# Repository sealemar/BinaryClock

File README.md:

BinaryClock
===========

More about the project is on my blog:

- [I talk about software](http://sealemar.blogspot.com/2014/02/binaryclock-binary-clock-diy.html)
- [I talk about hardware](http://sealemar.blogspot.com/2014/02/binaryclock-hardware.html)

Here I talk only about the tools which you will need to compile the software.

Tools I will need
-----------------

This is a list of tools you will (or may) need to work with the code. This list is described in more details on the [blog](http://sealemar.blogspot.com).

- [Make](http://www.gnu.org/software/make/manual/make.html) (*comes with every Unix based OS - Linux/Mac, etc.*)
- [Arduino software](http://arduino.cc/en/Main/Software)
- [Makefile by Sudar / Martin Oldfield](https://github.com/sudar/Arduino-Makefile)
- [colorgcc](https://github.com/colorgcc/colorgcc) (*optional, but is very handy when it comes to compiling code in the console/terminal*)
- [Exuberant ctags](http://ctags.sourceforge.net/) (*optional, but is very handy especially when it comes to Emacs or ViM*)

**For the emulator and tests:**
- gcc / clang (*at least one of these comes with every Unix based OS - Linux - gcc, MacOs - clang*)

**For the emulator:**
- ncurses (*comes with every Unix based OS*)

**For the vimproject (optional - read on):**
- ViM, [MacVim](https://code.google.com/p/macvim) for Mac

**For the schematic:**
- [Fritzing](http://fritzing.org)

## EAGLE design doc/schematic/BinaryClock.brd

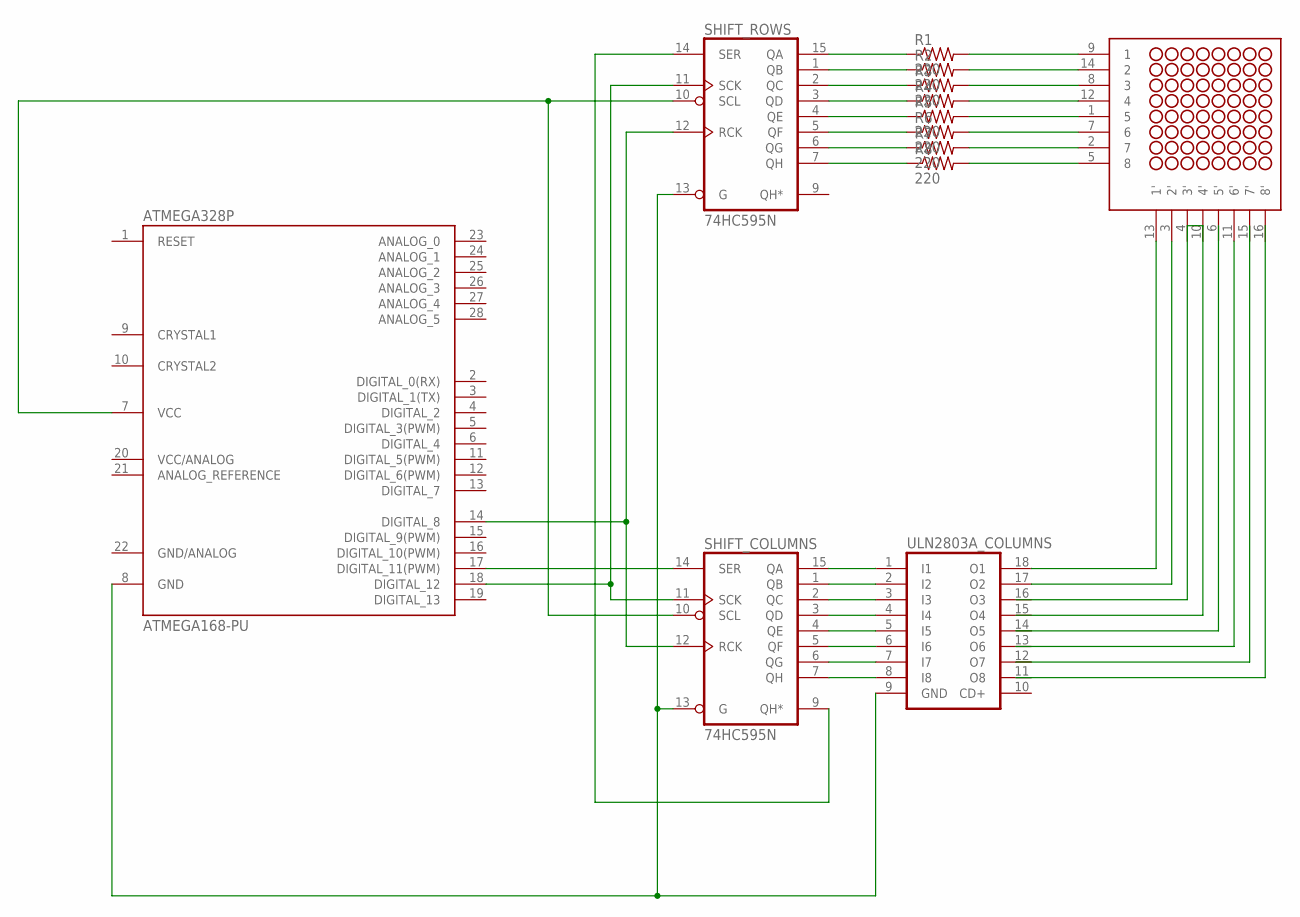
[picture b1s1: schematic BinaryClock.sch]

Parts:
ATMEGA328P: ATMEGA168-PU; DIL28-3
LD1088BS: NFM-12881BG-11
R1, R2, R3, R5, R6, R7, R8: 220; 0207/10
R4: R-US_0207/10; 0207/10
SHIFT_COLUMNS: 74HC595N; DIL16
SHIFT_ROWS: 74HC595N; DIL16
ULN2803A_COLUMNS: ULN2803A; DIL18

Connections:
GND: SHIFT_COLUMNS.8 (GND), SHIFT_ROWS.8 (GND)
GND/ANALOG: ATMEGA328P.22 (GND/ANALOG)
unnamed: SHIFT_COLUMNS.9 (QH*), SHIFT_ROWS.14 (SER)
unnamed: ATMEGA328P.17 (DIGITAL_11(PWM)), SHIFT_COLUMNS.14 (SER)
unnamed: ATMEGA328P.18 (DIGITAL_12), SHIFT_COLUMNS.11 (SCK), SHIFT_ROWS.11 (SCK)
unnamed: ATMEGA328P.14 (DIGITAL_8), SHIFT_COLUMNS.12 (RCK), SHIFT_ROWS.12 (RCK)
unnamed: LD1088BS.14 (2), R2.2
unnamed: SHIFT_COLUMNS.15 (QA), ULN2803A_COLUMNS.1 (I1)
unnamed: SHIFT_COLUMNS.1 (QB), ULN2803A_COLUMNS.2 (I2)
unnamed: SHIFT_COLUMNS.2 (QC), ULN2803A_COLUMNS.3 (I3)
unnamed: SHIFT_COLUMNS.3 (QD), ULN2803A_COLUMNS.4 (I4)
unnamed: SHIFT_COLUMNS.4 (QE), ULN2803A_COLUMNS.5 (I5)
unnamed: SHIFT_COLUMNS.5 (QF), ULN2803A_COLUMNS.6 (I6)
unnamed: SHIFT_COLUMNS.6 (QG), ULN2803A_COLUMNS.7 (I7)
unnamed: SHIFT_COLUMNS.7 (QH), ULN2803A_COLUMNS.8 (I8)
unnamed: ATMEGA328P.7 (VCC), SHIFT_COLUMNS.10 (SCL), SHIFT_ROWS.10 (SCL)
unnamed: R2.1, SHIFT_ROWS.1 (QB)
unnamed: R3.1, SHIFT_ROWS.2 (QC)
unnamed: R4.1, SHIFT_ROWS.3 (QD)
unnamed: R5.1, SHIFT_ROWS.4 (QE)
unnamed: R6.1, SHIFT_ROWS.5 (QF)
unnamed: R7.1, SHIFT_ROWS.6 (QG)
unnamed: R8.1, SHIFT_ROWS.7 (QH)
unnamed: R1.1, SHIFT_ROWS.15 (QA)
unnamed: ATMEGA328P.8 (GND), SHIFT_COLUMNS.13 (G), SHIFT_ROWS.13 (G), ULN2803A_COLUMNS.9 (GND)
unnamed: LD1088BS.8 (3), R3.2
unnamed: LD1088BS.12 (4), R4.2
unnamed: LD1088BS.1 (5), R5.2
unnamed: LD1088BS.7 (6), R6.2
unnamed: LD1088BS.2 (7), R7.2
unnamed: LD1088BS.5 (8), R8.2
unnamed: LD1088BS.9 (1), R1.2
unnamed: LD1088BS.13 (1'), ULN2803A_COLUMNS.18 (O1)
unnamed: LD1088BS.3 (2'), ULN2803A_COLUMNS.17 (O2)
VCC: SHIFT_COLUMNS.16 (VCC), SHIFT_ROWS.16 (VCC)

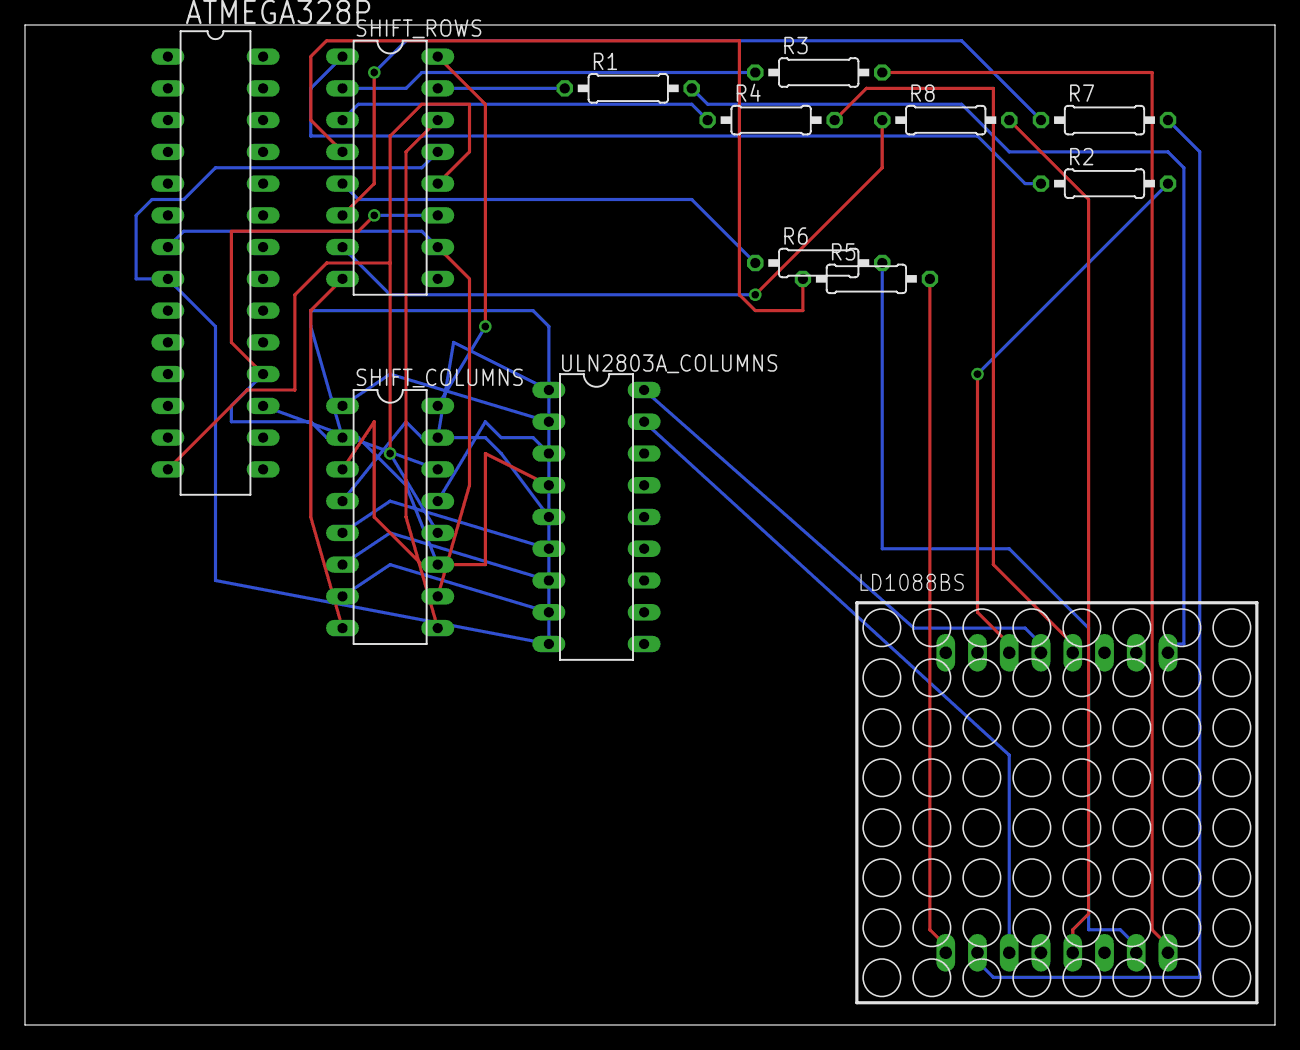
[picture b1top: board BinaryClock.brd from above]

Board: 2 copper layers, 100.0 x 80.0 mm, 13 parts (0 on the bottom side), 34 nets.

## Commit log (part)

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2013-11-09 introducing API, alphabet
2013-11-11 +) YouCompleteMe +) Added subdirectories: arduino, lib, emulator, test, include each of those have their own Makefile +) unit tests for clock::slidePattern()
2013-11-11 *) mainly work around Makefiles *) *.o -> obj/*.o *) *.d -> deps/*.d *) project.vim now creates etc/ dir when saving a session
2013-11-12 +) .gitignore + etc/ *) silent include dependencies and only if rule is not "clean" *) test/tests.c doesn't need #include <arch/clock_bits.h>
2013-11-12 +) .gitignore bin/, obj/, dep/ *) ar -v
2013-11-13 *) Now Makefile creates supplimentary directories only once
2013-11-13 +) Trying to make emulator to call clock_drawPattern()
2013-11-14 *) Makefile changes to make it compile and link on Raspberry Pi (ARM) as well as on x86
2013-11-14 *) Removed separate definition and switched from gcc back to clang
2013-11-14 +) Makefile distclean target. make clean - removes object files, dependency files, binaries make distclean - removes BUILD_DIR if set or OBJ_DIR, BIN_DIR, DEPS_DIR and ctags file
2013-11-14 *) Emulator works and draws the alphabet. To draw one character back press 'h' or 'k', to draw one character forward press any other key. Press Esc to quit
2013-11-15 *) This change reverses the patterns to bits counting from right to left
2013-11-15 +) lib/clock::clock_slideText() +) lib/clock::clock_slidePattern() *) Makefile.include always create ctags file
2013-11-15 +) Clock can slide any text. "Hello world!!!" sliding is implemented
2013-11-15 +) include/Makefile.include + -include stddef.h ---> got read of #define NULL 0
2013-11-15 +) lib/clock.c::clock_displayBinaryNumber() - not working yet
2013-11-15 lib/clock.c::clock_displayBinaryNumber() works correctly
2013-11-16 +) A little testing framework was implemented which produces this kind of output:
    --- tests.c:21 (main) - a test suite started ---
    --- ut_clock.c:239 (ut_clock_tests) - a test suite started ---
    Error: ut_clock.c:172 (test_clock_drawPattern_correct) - [-48] pattern CLOCK_ALPHABET[CLOCK_1] doesn't match the screen
    ----> test_ut/test_ut.c:21 (_runTestSuite) - [-48]
    --- ut_clock.c:239 (ut_clock_tests) - a test suite completed --- 4 test(s) ran. 3 succeded, 1 failed
    ----> test_ut/test_ut.c:21 (_runTestSuite) - [1]
2013-11-18 *) test_ut now prints which unit it currently runs
2013-11-18 +) lib/clock_time - working on the Binary Clock date/time functionality
2013-11-19 -) lib/arch/*, emulator/arch/*, test/arch/* Now clock_setPixel() is defined directly in lib/clock.h for simplicity
    +) test/.ycm_extra_conf.py - a separate YouCompleteMe configuration for
    tests
2013-11-19 +) test/ut_clock_time --- unit tests for lib/clock_time.c:clock_updateUptimeMillis()
    *) .ycm_extra_conf.py seems to handle sorces correctly now
2013-11-19 *) lib/clock_time.c::DateTime now has milliseconds +) unit tests for lib/clock_time.c::clock_addMillisToDateTime()
2013-11-20 +) A separate module which incapsulates DateTime functionality
    *) A unit test for dateTime_addMilliseconds() was rewritten to work with
    a new module
2013-11-20 +) test_dateTime_normalize_handlesOverflows()
2013-11-22 *) test/ut_date_time.c - underflows
2013-11-25 +) include/common.h --- version information +) emulator --- sections: - Banner - ClockFace - Buttons - Notes
2013-11-25 +) emulator/clock_extra --- buttons
2013-11-27 +) include/common.h::Call() -- a macro Call(function) makes a function call taking PARAM_CHECKS macro into consideration. If the macro is defined, ContinueError(functionResult, "%d"); will be called 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
    +) lib/clock_state.h -- clock state to pass with every iteration of main
    loop
    +) lib/clock_main -- working on clock_update(ClockState *) function
    which will be called from main loop
    *) lib/clock_time::clock_updateUptimeMillis() now takes a pointer to
    unsigned long to get and set lastMillis
2013-11-27 The first somewhat working version of BinaryClock emulator!!! At startup it shows a banner, then starts Binary Clock mode
    +) lib/clock_main::clock_init()
    +) lib/clock_main::clock_state_*() implementation of some functions
2013-11-27 *) Optimization of clock_state_showTime() and clock_state_showDate() by adding ClockState::oldDateTime. ClockState::dateTime gets updated at the beginning of clock_update() and ClockState::oldDateTim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
2013-11-27 *) Working towards implementation for the buttons
2013-11-27 *) Working towards implementation of the buttons
2013-11-28 +) lib/clock_button and corresponding unit tests. Current implementation can operate on up to 4 buttons
2013-11-28 +) emulator/emulator_button -- buttons work. Not connected yet
2013-11-28 +) lib/clock_state::ClockState.frameMillis -- current frame time (for animation), i.e. those steps which slide text can use it to show the next frame only after the _frameMillis_ exceeds some amount
2013-11-28 +) lib/clock_main::clock_state_setTime()
2013-11-29 *) lib/clock_main::clock_state_setTime() blinks time while it is being set
2013-11-29 +) emulator/emulator_button -- now displays information next to each button with what that button does in the current context
2013-11-29 +) lib/date_time::date_time_dateToStr(const DateTime *dt, char str[DATE_TIME_DATE_STR_SIZE]) prints date from _dt_ to _str_ in format MMM DD YYYY
    +) lib/date_time::date_time_timeToStr(const DateTime *dt, char str[DATE_TIME_TIME_STR_SIZE])
    prints time from _dt_ to _str_ in format
    hh:mm:ss
    +) unit tests for both functions
    +) lib/date_time::DateTimeMonthsStr --- an array of three letter months
2013-11-29 +) lib/clock_main::clock_state_showTimeBigEndian()
2013-11-30 +) lib/date_time::date_time_daysInMonth() returns a quantity of days in a month
    +) test/test_ut/test_ut.h::assert_number(number, expected) asserst any number against
    expected
    +) test/test_ut/test_ut.h::assert_errorCode(function, expectedErrorCode)
    asserts a function against an expected error code
2013-11-30 *) include/Makefile.include::CC_c_FLAGS + -Wextra -Werror
    *) test/test_ut/test_ut.h::assert_errorCode -> assert_function
2013-11-30 *) All extern functions which an implementation must or may want to (for some funcitons) override are now declared in lib/clock_extern_functions.h and stubbed to NULL by default
    +) lib/clock_extern_functions.c::clock_initDateTime(DateTime *) an
    implementation may define this function. If it is not NULL,
    lib/clock_main.c::clock_init(ClockState *) will call it to initialize
    ClockState->DateTime. I.e. an implementation may define the function to
    set the date and time to current date and time
2013-11-30 +) lib/clock_extern::clock_extern_clearScreen(). The implementation may override this to optimize clock_clearScreen() behavior. By default it does Call( clock_drawPattern(ClockAlphabet[CLOCK_BLANK]) 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
    *) Refactoring
2013-11-30 +) More Call*() macros
2013-11-30 *) Call*() around some more functions, which I missed in the last commit
2013-12-01 +) -D _BSD_SOURCE in emulator/Makefile for localtime_r() on Linux
2013-12-01 +) lib/clock_main added segue from CLOCK_STATE_SHOW_TIME_BIG_ENDIAN to CLOCK_STATE_SHOW_DATE_BIG_ENDIAN and vice versa
2013-12-02 +) working on lib/clock_events
    +) lib/clock_alphabet + '(' and ')'
    +) lib/clock_alphabet::clock_alphabet_getIndexByCharacter() now
    recognizes
    SMILEY_FACE_SMILE - '\001'
    SMILEY_FACE_SAD - '\002'
    *) lib/clock::clock_getAlphabetIndexByCharacter() ->
2013-12-03 *) Still working on lib/clock_events
2013-12-04 *) minor changes to lib/clock_event.h macros
2013-12-04 +) test/test_ut/test_ut.h::assert_false()
2013-12-05 *) Makefile -- don't cancel make job if Arduino make fails
2013-12-05 +) lib/date_time::date_time_calculateDayOfWeek(int year, int month, int day)
    implemented using
    Gauss's algorithm
    to determine day of week in Gregorian Calendar
    http://en.wikipedia.org/wiki/Determination_of_the_day_of_the_week#Formulas_derived_from_Gauss.27s_algorithm
    +) unit tests
    +) some changes to lib/clock_event
2013-12-05 *) fixed typos in functions' names
2013-12-06 !! This is an intermediate version !! Can not be compiled
    *) working on lib/clock_event
    -) lib/date_const
    +) lib/date_time strings for days of week
    *) lib/date_time::date_time_daysInMonth() now takes year and month
    separately, instead of taking a pointer to DateTime
2013-12-07 *) working on lib/clock_event +) test_clock_event_getEventDetails_correct() *) fixed some compilation issues with PARAM_CHECKS off *) fixed a bug in lib/date_time.c::_dayOfWeek() in Gauss's algorithm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
2013-12-07 +) test/ut_clock_event::test_clock_event_initList_correct() +) test/ut_clock_event::test_clock_event_updateList_correct()
    *) some unit tests in test/ut_clock_event were changed to have data
    declaration in the beginning and then code checking the data in the end
    +) ut_test -- assert_number_ex(), assert_int_ex(), assert_str_ex()
2013-12-07 +) lib/clock_event::ClockEvent.yearCalculated -- the year which the event is calculated for (initially CLOCK_EVENT_YEAR_NOT_CALCULATED)
    *) lib/clock_event::ClockEvent.year ->
    lib/clock_event::ClockEvent.yearStarted
2013-12-09 +) lib/clock_alphabet::CLOCK_TICK --- "'" +) lib/clock_event::clock_event_toStr() +) lib/clock_event::clock_event_findClosestFromList() +) lib/clock_main::checkButton() macro +) lib/clock_main::clock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
    *) lib/clock_main::slideText() now accepts an optional callback which should be
    called when the slideText() completes. If it is not NULL, _nextState_ and
    _nextStepMillis_ will be ignored and the callback will be called.
2013-12-09 *) fixed comments for ClockEvent.name size
2013-12-09 *) comments
2013-12-09 *) working on Arduino part -- compiles !!! *) lib/*.h --> \#ifdef __cplusplus extern "C" { \#endif
2013-12-10 +) lib/clock_event::clock_event_yearInfoToStr() +) lib/clock_state::clock_state_showEventYearInfo() +) test/ut_clock_event::test_clock_event_yearInfoToStr_correct()
2013-12-12 +) arduino works!!!
2013-12-13 *) changed travelling row bit to travelling column bit to eliminate this nasty flickering:
    http://forum.arduino.cc/index.php?topic=204377
    https://www.youtube.com/watch?v=ivCGI88enM8
2013-12-19 +) arduino/Makefile --- ISP definitions +) ULN2803 on hardware side to not overstress on a walking column *) the code in arduino/binary_clock.ino is changed to account for the ULN
2014-01-02 +) doc/schematic/ Eagle CAD schematic and Fritzing CAD project
2014-01-13 arduino/binary_clock.ino: no pull-down resistors on buttons, uses internal ATMEGA328 pull-up resistors instead. Uses pins 2-5 for buttons. No duty cycle as 260 Ohm resistors on rows with 3 AA batteri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
2014-01-15 Adding 'LED Matrix LD1088-BS' Fritzing part
2014-01-15 Fritzing schematic
2014-01-15 +) Fritzing part - FTDI Basic Male Header +) FTDI on schematics
2014-01-17 Schematics is ready for 2 x 74HC595, ULN2803A
2014-01-17 Don't erase Atmega flash on make upload
2014-01-17 License: BSD -> Apache 2.0
2014-01-19 arduino/binary_clock.ino: introduced update intervals, one for interacting with the clock and the other for displaying the data on the screen. The intervals are supposed to save power consumption
2014-01-19 arduino/binary_clock.ino: fixed wrong comment
2014-02-01 README.md
2014-02-01 -) Eagle CAD files *) README.md Fritzing home page fix
2014-02-01 +) doc/photos - photos of my BinaryClock
2014-02-01 *) README.md points to my blog *) include/logger.h stringification macros were moved to include/common.h *) lib/clock_main.c shows banner on the start screen
2014-02-01 *) README.md line break
2014-02-01 README.md bullet list on blog links
2014-02-02 *) Fixed error in schematics as per http://forum.arduino.cc/index.php?topic=204377.msg1572493#msg1572493
2014-02-08 *) lib/clock_event.h - fixed typos in comments
2014-04-13 *) Fixed clock_event_updateList() logic. If the date was first increased and then decreased and that manipulation went through a ClockEvent, then that ClockEvent will stay calculated as for the next 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

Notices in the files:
parts and their libraries:
eagle-library-edeca.net-v5: This is v1 and is licensed under the Creative Commons (Attribution-Non-Commercial-Share Alike 2.0 UK)
